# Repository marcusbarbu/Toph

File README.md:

# Toph
## What is it?
* Final project for ECE-UY 4144 Intro to Embedded Systems Design.
* A modular solution to wall sensing

## How?
* Miniflex contains the physical modules used in the Toph system.
* Toph is written in C using minimal Arduino-specific syntax and macros.
* Toph is extendable.  New modules can be added with a single line of code.

## Why?
* An exercise in embedded design, from hardware to software.

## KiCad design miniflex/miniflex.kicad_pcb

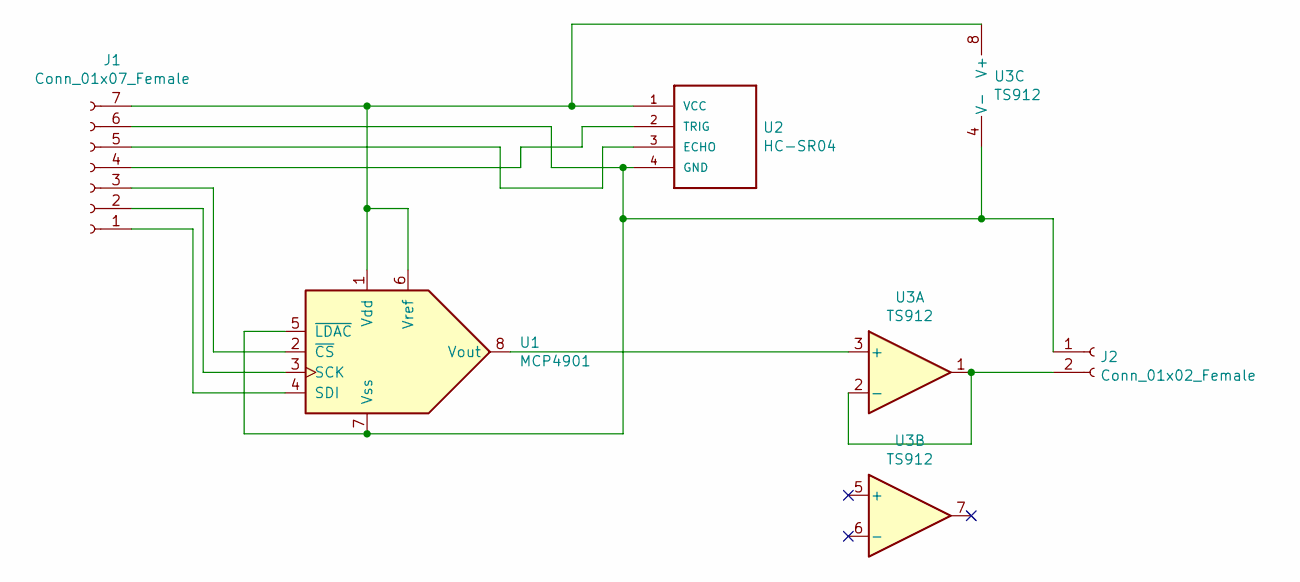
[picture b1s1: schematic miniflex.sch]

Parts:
J1: Conn_01x07_Female; PinSocket_1x07_P2.54mm_Vertical
J2: Conn_01x02_Female; PinSocket_1x02_P2.54mm_Vertical
U1: MCP4901; DIP-8_W7.62mm_Socket
U2: HC-SR04; XCVR_HC-SR04
U3: TS912; DIP-8_W7.62mm_Socket

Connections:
unnamed: J1.1, U1.4 (SDI)
unnamed: J1.2, U1.3 (SCK)
unnamed: J1.3, U1.2 (~CS)
unnamed: J1.4, U2.2 (TRIG)
unnamed: J1.5, U2.3 (ECHO)
unnamed: J1.6, J2.1, U1.5 (~LDAC), U1.7 (Vss), U2.4 (GND), U3.4 (V-)
unnamed: J1.7, U1.1 (Vdd), U1.6 (Vref), U2.1 (VCC), U3.8 (V+)
unnamed: J2.2, U3.1, U3.2 (-)
unnamed: U1.8 (Vout), U3.3 (+)

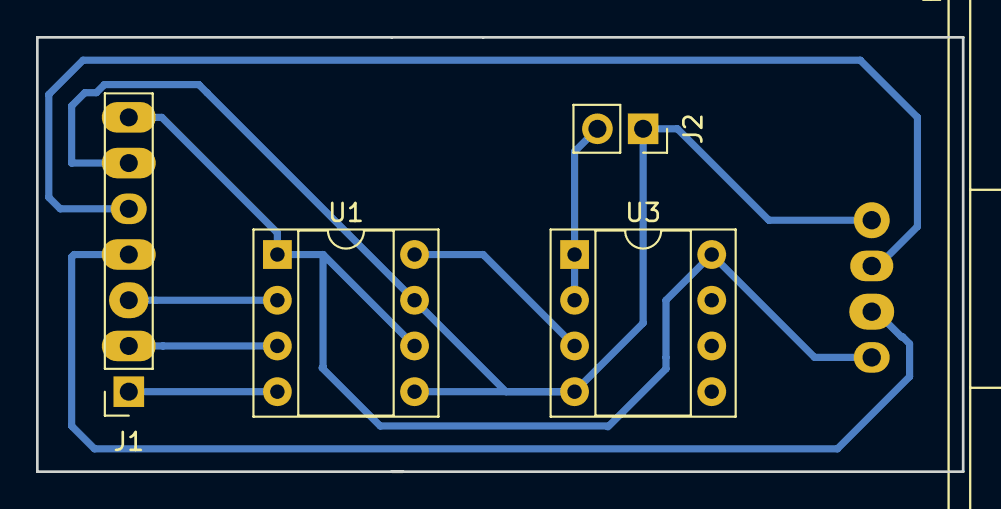
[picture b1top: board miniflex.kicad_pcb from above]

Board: 2 copper layers, 51.4 x 24.1 mm, 5 parts (0 on the bottom side), 9 nets.

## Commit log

2019-01-14 added license
